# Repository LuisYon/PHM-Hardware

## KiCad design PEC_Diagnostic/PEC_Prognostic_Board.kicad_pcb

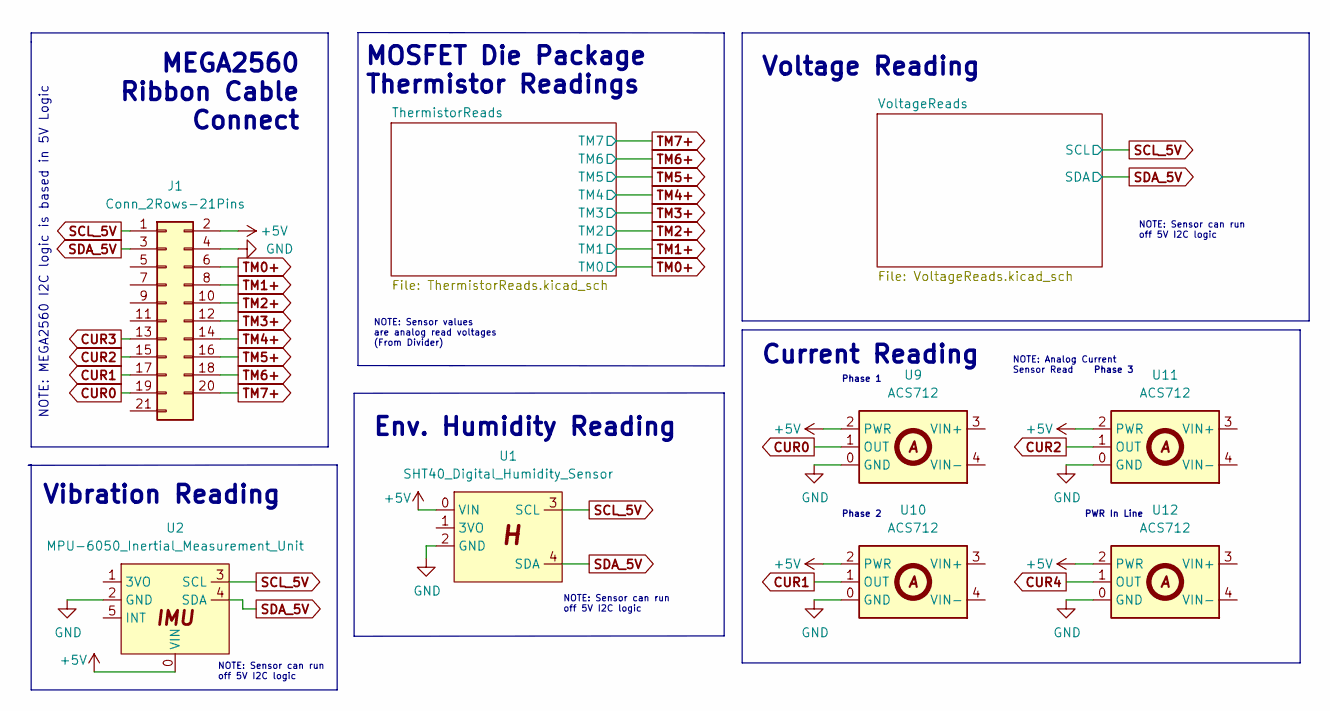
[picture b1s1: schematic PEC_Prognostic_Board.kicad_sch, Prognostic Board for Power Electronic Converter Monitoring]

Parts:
J1: Conn_2Rows-21Pins; PinHeader_2x10_P2.54mm_Vertical
U1: SHT40_Digital_Humidity_Sensor; SHT40_BB
U2: MPU-6050_Inertial_Measurement_Unit; MPU6050_BB
U9, U10, U11, U12: ACS712

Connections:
+5V: J1.2, U9.2 (PWR), U10.2 (PWR), U11.2 (PWR), U12.2 (PWR); also elsewhere on the board
CUR0: J1.19, U9.1 (OUT)
CUR1: J1.17, U10.1 (OUT)
CUR2: J1.15, U11.1 (OUT)
CUR3: J1.13
CUR4: U12.1 (OUT)
GND: J1.4, U1.2 (GND), U2.2 (GND); also elsewhere on the board
SCL_5V: J1.1, U1.3 (SCL), U2.3 (SCL); also elsewhere on the board
SDA_5V: J1.3, U1.4 (SDA), U2.4 (SDA); also elsewhere on the board
TM0+: J1.6; also elsewhere on the board
TM1+: J1.8; also elsewhere on the board
TM2+: J1.10; also elsewhere on the board
TM3+: J1.12; also elsewhere on the board
TM4+: J1.14; also elsewhere on the board
TM5+: J1.16; also elsewhere on the board
TM6+: J1.18; also elsewhere on the board
TM7+: J1.20; also elsewhere on the board

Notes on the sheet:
Current Reading
MOSFET Die Package Thermistor Readings
NOTE: Sensor can run off 5V I2C logic
Phase 2
Voltage Reading
NOTE: Analog Current Sensor Read
Vibration Reading
NOTE: Sensor values are analog read voltages (From Divider)
PWR In Line
Phase 1
NOTE: MEGA2560 I2C logic is based in 5V Logic
MEGA2560 Ribbon Cable Connect
Phase 3
Env. Humidity Reading

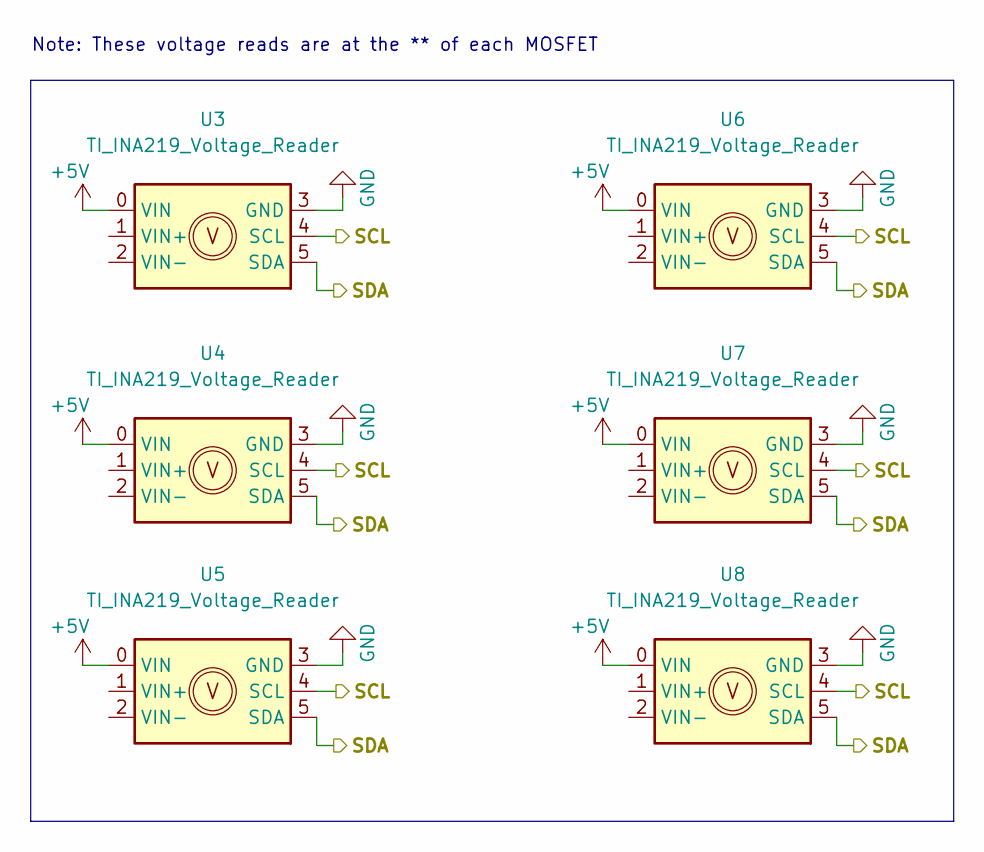
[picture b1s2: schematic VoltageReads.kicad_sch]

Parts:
U3, U4, U5, U6, U7, U8: TI_INA219_Voltage_Reader; INA219

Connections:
GND: U3.3 (GND), U4.3 (GND), U5.3 (GND), U6.3 (GND), U7.3 (GND), U8.3 (GND); also elsewhere on the board
SCL_5V: U3.4 (SCL), U4.4 (SCL), U5.4 (SCL), U6.4 (SCL), U7.4 (SCL), U8.4 (SCL); also elsewhere on the board
SDA_5V: U3.5 (SDA), U4.5 (SDA), U5.5 (SDA), U6.5 (SDA), U7.5 (SDA), U8.5 (SDA); also elsewhere on the board

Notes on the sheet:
Note: These voltage reads are at the ** of each MOSFET

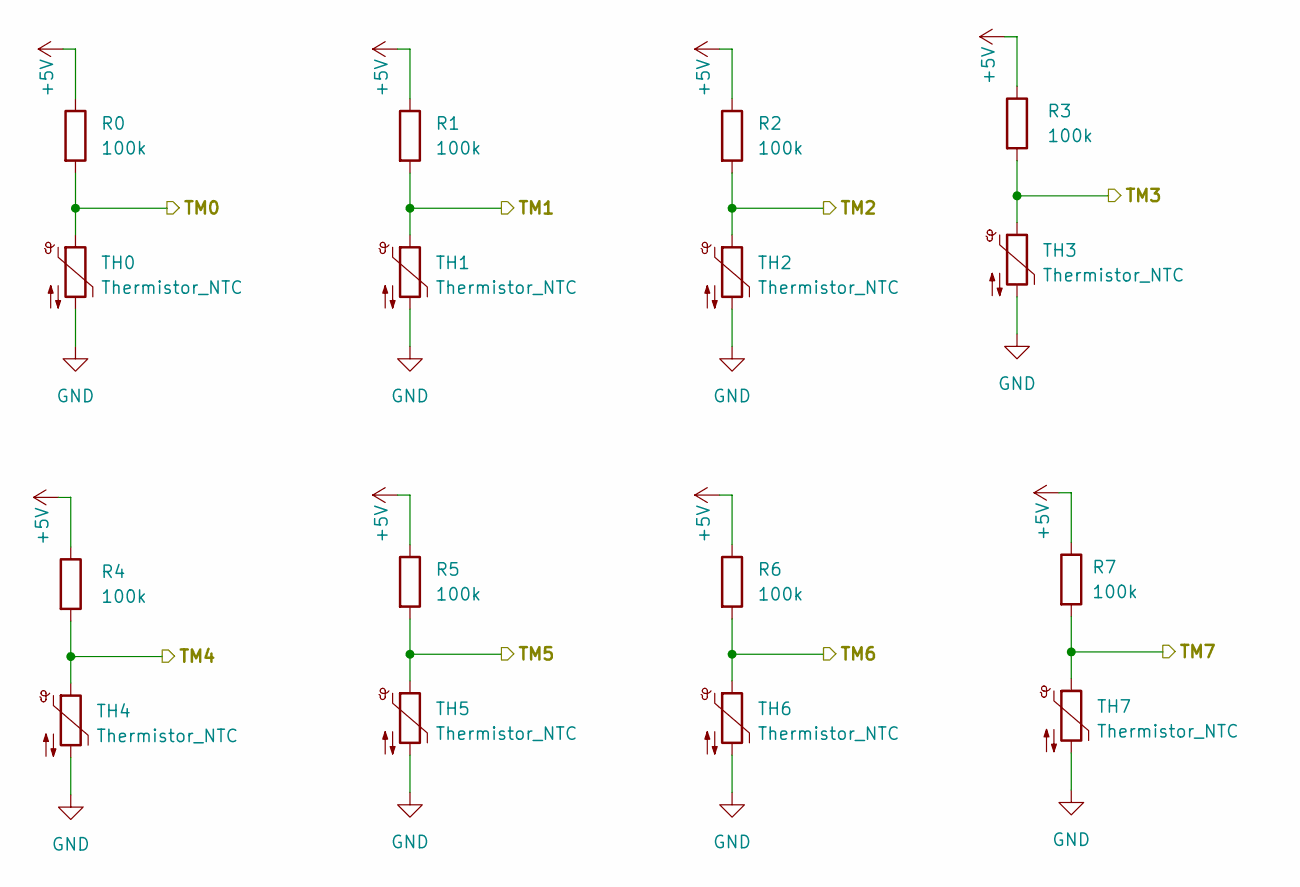
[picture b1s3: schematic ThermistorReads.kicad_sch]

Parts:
R0, R1, R2, R3, R4, R5, R6, R7: 100k; R_Box_L8.4mm_W2.5mm_P5.08mm
TH0, TH1, TH2, TH3, TH4, TH5, TH6, TH7: Thermistor_NTC; PinHeader_1x03_P2.54mm_Vertical

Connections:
+5V: R0.1, R1.1, R2.1, R3.1, R4.1, R5.1, R6.1, R7.1; also elsewhere on the board
GND: TH0.2, TH1.2, TH2.2, TH3.2, TH4.2, TH5.2, TH6.2, TH7.2; also elsewhere on the board
TM0+: R0.2, TH0.1; also elsewhere on the board
TM1+: R1.2, TH1.1; also elsewhere on the board
TM2+: R2.2, TH2.1; also elsewhere on the board
TM3+: R3.2, TH3.1; also elsewhere on the board
TM4+: R4.2, TH4.1; also elsewhere on the board
TM5+: R5.2, TH5.1; also elsewhere on the board
TM6+: R6.2, TH6.1; also elsewhere on the board
TM7+: R7.2, TH7.1; also elsewhere on the board

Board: 4 copper layers, 29 parts (0 on the bottom side), 15 nets, no tracks yet.

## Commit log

2022-09-21 Initial Commit
    Schematic overlay completed. Basic PCB started with footprints attached. Pinout assignments on the Voltage Readers, IMU, and T&H sensor need to be adjusted.
2022-09-21 PCB Updated
    Set stackup layers
2022-09-22 Mid push
    Removed cavity
2022-09-25 Updated Board Size
    Updated the PCB size and attached images of the protoboard assembly.
2022-10-01 Misc. Push
    Added Progress Images
2022-11-01 Overhauled traces. Added polygon pours and updated figures
